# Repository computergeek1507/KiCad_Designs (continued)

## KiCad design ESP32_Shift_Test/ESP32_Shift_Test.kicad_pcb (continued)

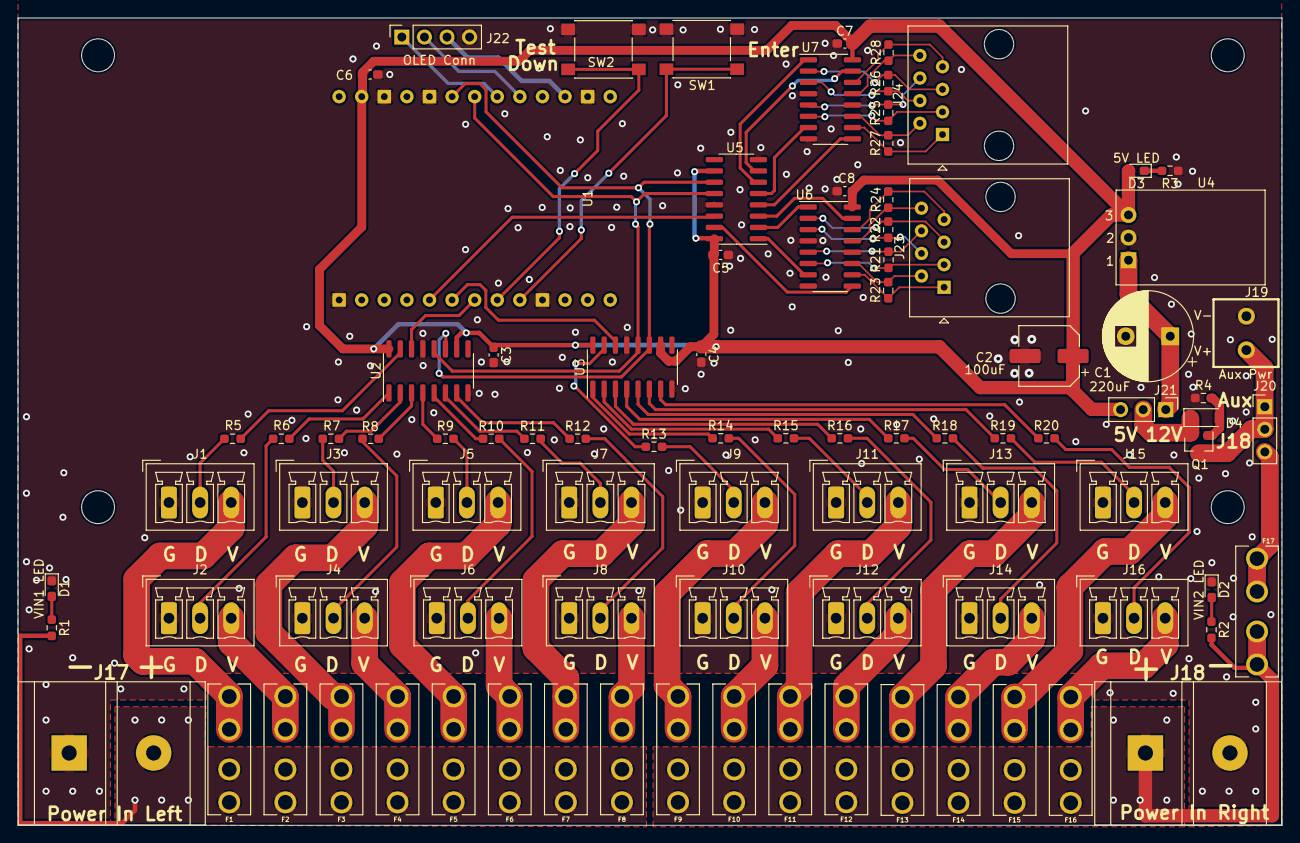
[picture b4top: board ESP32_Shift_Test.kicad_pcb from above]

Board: 2 copper layers, 142.1 x 90.8 mm, 91 parts (0 on the bottom side), 94 nets.

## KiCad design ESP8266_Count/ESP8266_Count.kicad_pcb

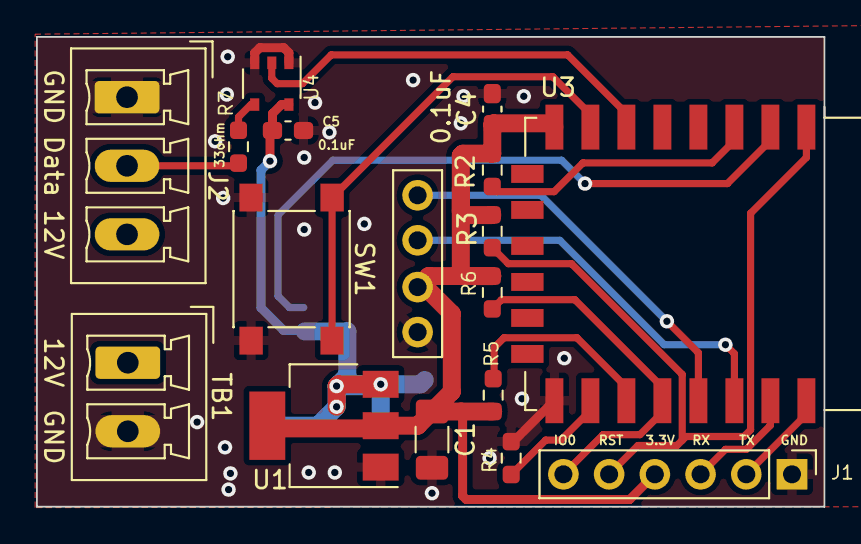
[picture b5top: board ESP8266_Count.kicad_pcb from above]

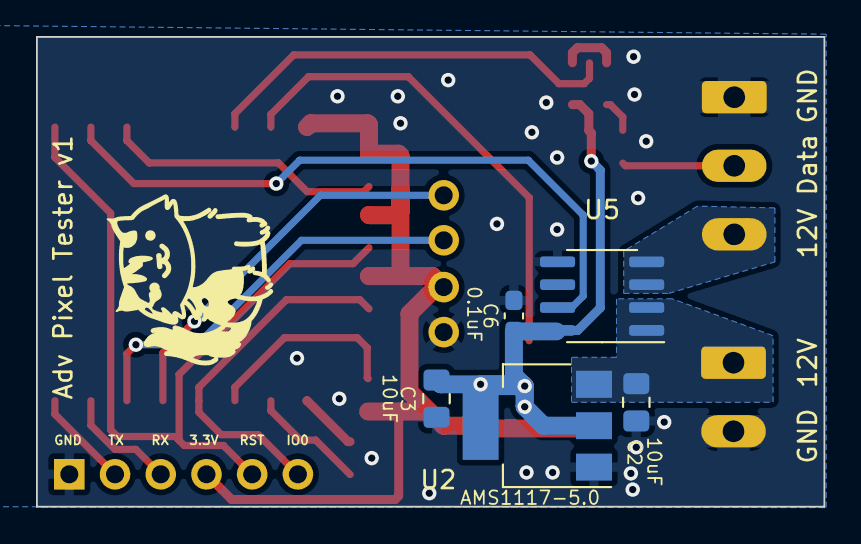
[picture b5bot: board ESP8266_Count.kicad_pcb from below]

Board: 2 copper layers, 43.7 x 26.1 mm, 22 parts (5 on the bottom side), 19 nets.

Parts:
C1: 100uF; C_1206_3216Metric_Pad1.33x1.80mm_HandSolder
C2, C3: 10uF; C_0805_2012Metric_Pad1.18x1.45mm_HandSolder
C4, C5, C6: 0.1uF; C_0603_1608Metric_Pad1.08x0.95mm_HandSolder
J1: PMG; PinHeader_1x06_P2.54mm_Vertical
J2: String1; PhoenixContact_MCV_1,5_3-G-3.81_1x03_P3.81mm_Vertical
J3: OLED; OLED-SSD1306-128X64-I2C-THT_2HOLE
R2, R3, R4, R5, R6: 10K; R_0603_1608Metric_Pad0.98x0.95mm_HandSolder
R7: 33ohm; R_0603_1608Metric_Pad0.98x0.95mm_HandSolder
SW1: SW_Push; SW_Push_1P1T_NO_6x6mm_H9.5mm
TB1: Power In; PhoenixContact_MCV_1,5_2-G-3.81_1x02_P3.81mm_Vertical
U1: AMS1117-3.3; SOT-223-3_TabPin2
U2: AMS1117-5.0; SOT-223-3_TabPin2
U3: ESP-12E
U4: 74AHCT1G125; TSOP-5_1.65x3.05mm_P0.95mm
U5: ACS706xLC-05C; SOIC-8_3.9x4.9mm_P1.27mm

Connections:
+3.3V: C1.1, C4.1, J1.4, J3.3, R2.1, R3.1, R5.1, R6.1, U1.2 (VO), U3.8 (VCC)
+5V: C3.1, C5.1, C6.1, U1.3 (VI), U2.2 (VO), U4.5 (VCC), U5.8 (VCC)
/DOUT1: J2.2, R7.1
/EN: R2.2, U3.3 (EN)
/GPIO2: R5.2, U3.17 (GPIO2)
/GPIO15: R4.1, U3.16 (GPIO15)
GND: C1.2, C2.2, C3.2, C4.2, C5.2, C6.2, J1.1, J2.1, J3.4, R4.2, SW1.2, TB1.2, U1.1 (GND), U2.1 (GND), U3.15 (GND), U4.1, U4.3 (GND), U5.5 (GND)
GPIO0: J1.6, R6.2, U3.18 (GPIO0)
I2C_SCL: J3.2, U3.20 (GPIO5)
I2C_SDA: J3.1, U3.19 (GPIO4)
IN1: U3.2 (ADC), U5.7 (VOUT)
unnamed: R7.2, U4.4
OUT1: U3.6 (GPIO12), U4.2
RST: J1.5, R3.2, U3.1 (~RST)
RXD: J1.3, U3.21 (GPIO3/RXD)
SW1: SW1.1, U3.7 (GPIO13)
TXD: J1.2, U3.22 (GPIO1/TXD)
VIN1: C2.1, TB1.1, U2.3 (VI), U5.1 (IP+), U5.2 (IP+)
VOUT1: J2.3, U5.3 (IP-), U5.4 (IP-)

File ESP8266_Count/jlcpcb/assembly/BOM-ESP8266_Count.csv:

Comment,Designator,Footprint,LCSC
0.1uF,"C4,C5,C6",C_0603_1608Metric_Pad1.08x0.95mm_HandSolder,C14663
10uF,"C2,C3",C_0805_2012Metric_Pad1.18x1.45mm_HandSolder,C15850
33ohm,R7,R_0603_1608Metric_Pad0.98x0.95mm_HandSolder,C23140
10K,"R2,R3,R4,R5,R6",R_0603_1608Metric_Pad0.98x0.95mm_HandSolder,C25804
ACS706xLC-05C,U5,SOIC-8_3.9x4.9mm_P1.27mm,C465515
AMS1117-3.3,U1,SOT-223-3_TabPin2,C6186
AMS1117-5.0,U2,SOT-223-3_TabPin2,C6187
74AHCT1G125,U4,TSOP-5_1.65x3.05mm_P0.95mm,C7484
ESP-12E,U3,ESP-12E,C89297
100uF,C1,C_0805_2012Metric_Pad1.18x1.45mm_HandSolder,
SW_Push,SW1,SW_Push_1P1T_NO_6x6mm_H9.5mm,
